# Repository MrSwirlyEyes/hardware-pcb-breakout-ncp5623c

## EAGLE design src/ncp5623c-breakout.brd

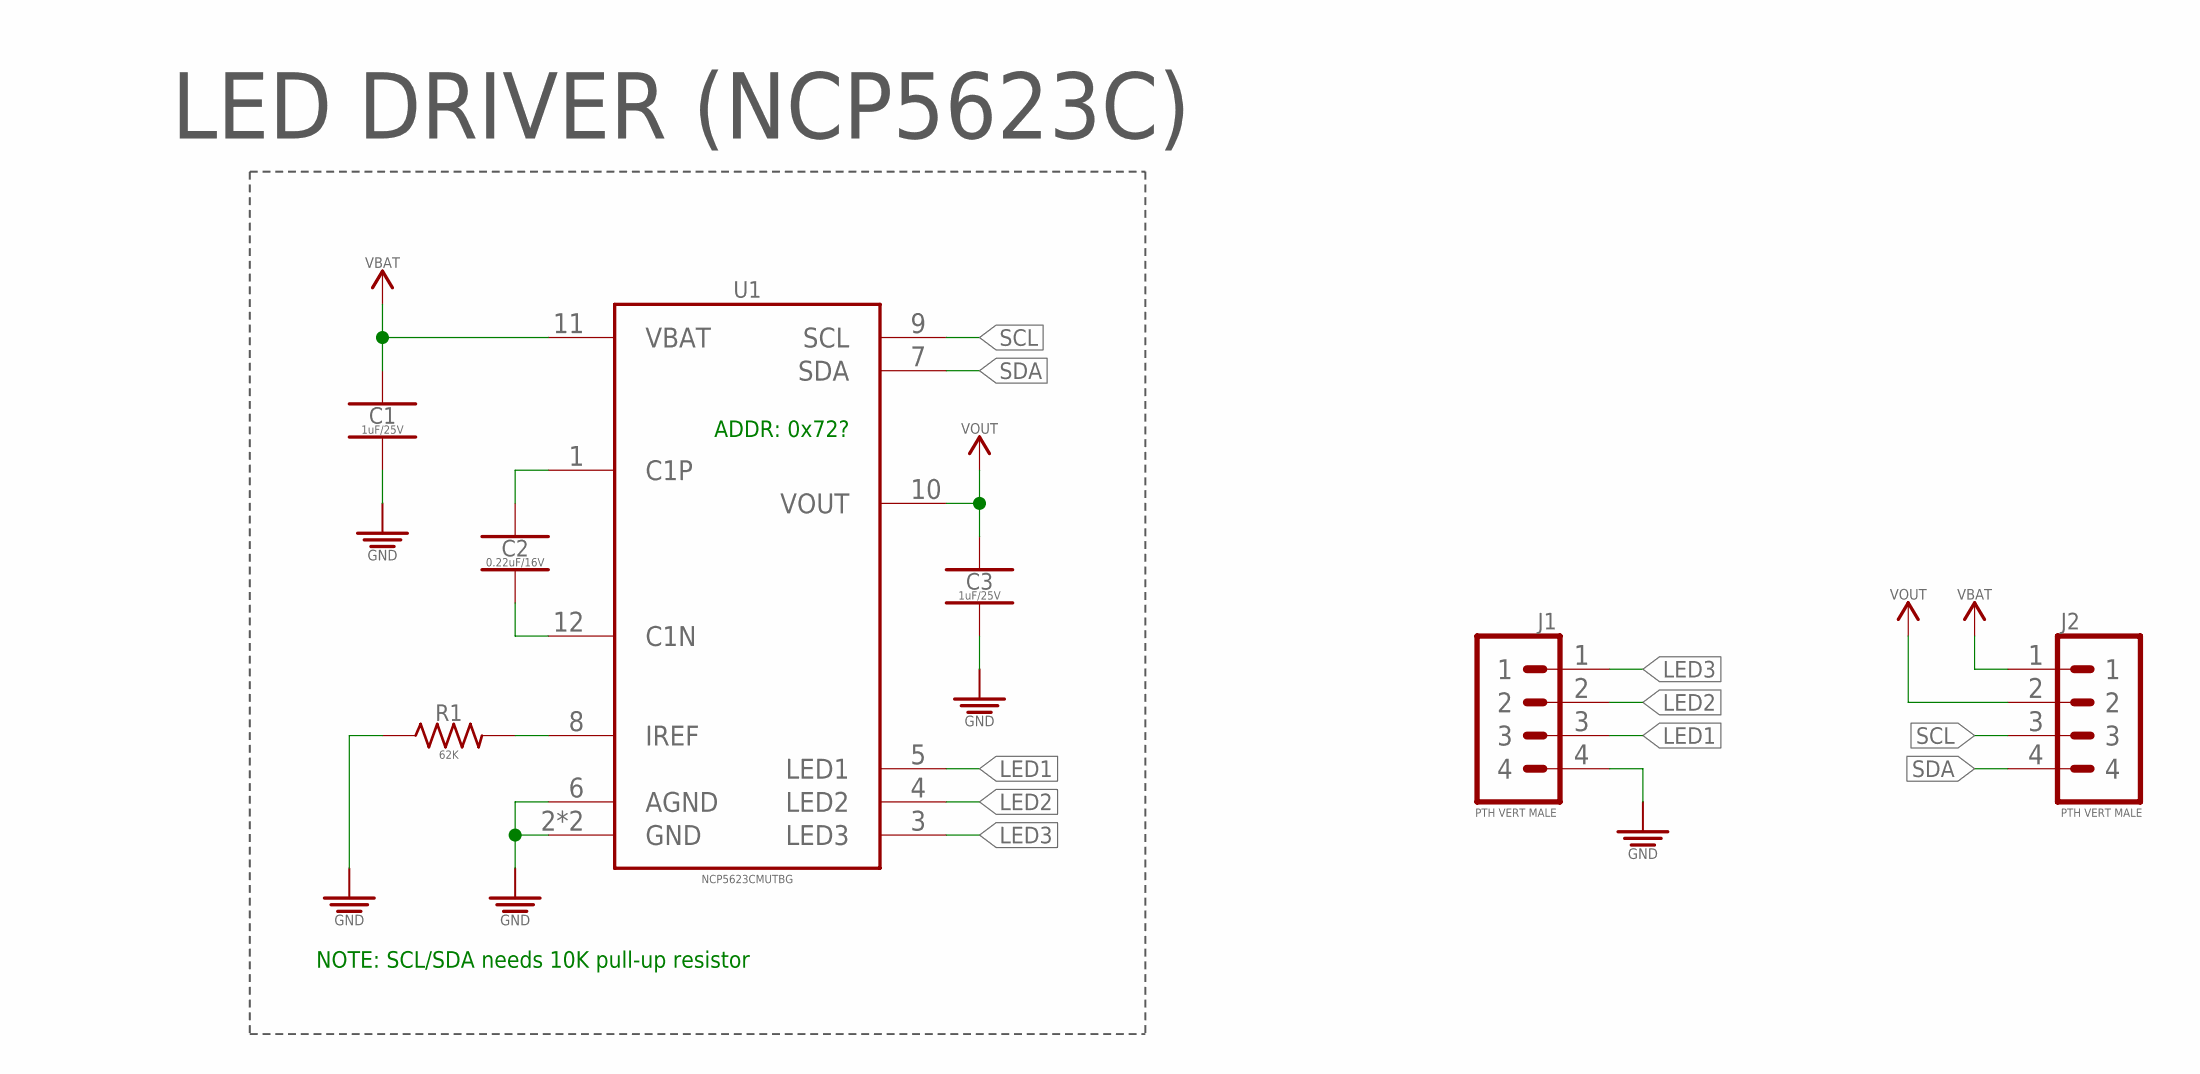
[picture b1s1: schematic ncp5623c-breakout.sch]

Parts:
C1, C3: 1uF/25V; CAPC1005X55_SMD-0402
C2: 0.22uF/16V; CAPC1005X55_SMD-0402
J1, J2: PTH VERT MALE; HDRV4W64P254_1X4_1016X254X838B
R1: 62K; RESC1005X35_SMD-0402
U1: NCP5623CMUTBG; SON40P200X200X80-11T57X90N

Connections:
GND: C1.2, C3.2, J1.4, R1.1, U1.2 (GND), U1.6 (AGND), U1.EP (GND)
LED1: J1.3, U1.5 (LED1)
LED2: J1.2, U1.4 (LED2)
LED3: J1.1, U1.3 (LED3)
unnamed: C2.2, U1.12 (C1N)
unnamed: C2.1, U1.1 (C1P)
unnamed: R1.2, U1.8 (IREF)
SCL: J2.3, U1.9 (SCL)
SDA: J2.4, U1.7 (SDA)
VBAT: C1.1, J2.1, U1.11 (VBAT)
VOUT: C3.1, J2.2, U1.10 (VOUT)

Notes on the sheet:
LED DRIVER (NCP5623C)
NOTE: SCL/SDA needs 10K pull-up resistor
ADDR: 0x72?

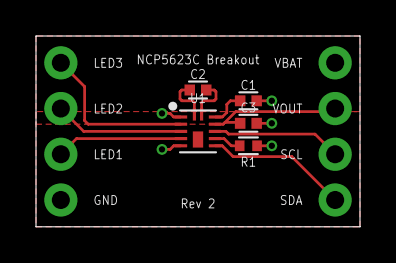
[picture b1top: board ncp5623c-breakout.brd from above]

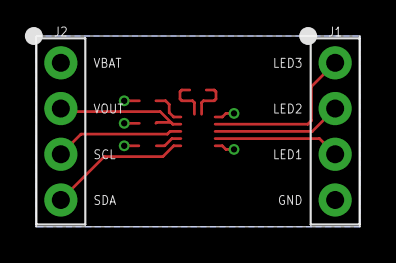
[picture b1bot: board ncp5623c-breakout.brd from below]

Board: 2 copper layers, 18.0 x 10.6 mm, 7 parts (2 on the bottom side), 11 nets.

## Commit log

2021-01-12 [Rev 1] - Initialize repo.
2021-08-11 Update CAM files.
